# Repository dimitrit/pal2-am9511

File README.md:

AM9511 Module for the PAL-2
===========================

The AMD AM9511 Arithmetic Processing Unit, first produced in the late 
1970s, provides hardware support for high performance fixed and floating 
point arithmetic and a variety of floating point trigonometric and 
mathematical operations, for use with microprocessors of that period.

This repository provides schematics and board design for a module that
can be connected to the PAL-2 Expansion interface.

The design is adapted from the work of Harris[1], who in turn based 
his implementation on designs by Kissel and Currie[2] in which they 
developed an experiment using a MOS 6502 microprocessor to control 
four AM9511A floating-point arithmetic units, and from Hart’s 
MICROCRUNCH[3] which also used the AM9511A (Intel 8231A) interfaced 
with a (Rockwell) 6502.

See [am9511-6502-description.pdf](am9511-6502-description.pdf) for a
full description of the interface circuit design and 
[am9511-6502-schematic.pdf](am9511-6502-schematic.pdf) for the schematic.

The specification here anticipates the use of an AM9511A clocked at
4 MHz. However, the same design will work with earlier versions of the 
AM9511, by setting JP to 2Mhz or by swapping the 4 MHz clock oscillator 
with a unit of an appropriately lower speed.

The `logic` folder contains the programming details for the ATF16V8B
used in the circuit, as produced by [Galette](https://github.com/simon-frankau/galette) 
from the `am9511-logic.pld` source file. The provided JEDEC file
(`am9511-logic.jed`) can be easily programmed into an ATF16V8B using 
[minipro](https://gitlab.com/DavidGriffith/minipro).

Also included in the `docs` folder are source documents cited below, as 
well as datasheets and supplementary documents for the AM9511.

---
1. Harris, CE: "AM9511 Interface Module for the 6502"; July 2025; [GitHub](https://github.com/ceharris/am9511-6502)
2. Kissel, R and Currie, J: "Hardware Math for the 6502 Microprocessor"; 
   July 1985; NASA TM-86517
3. Hart, J: "MICROCRUNCH: An Ultra-Fast Arithmetic Computing System 
   (part 1)"; August 1981; MICRO - the 6502/6809 Journal (No. 39)

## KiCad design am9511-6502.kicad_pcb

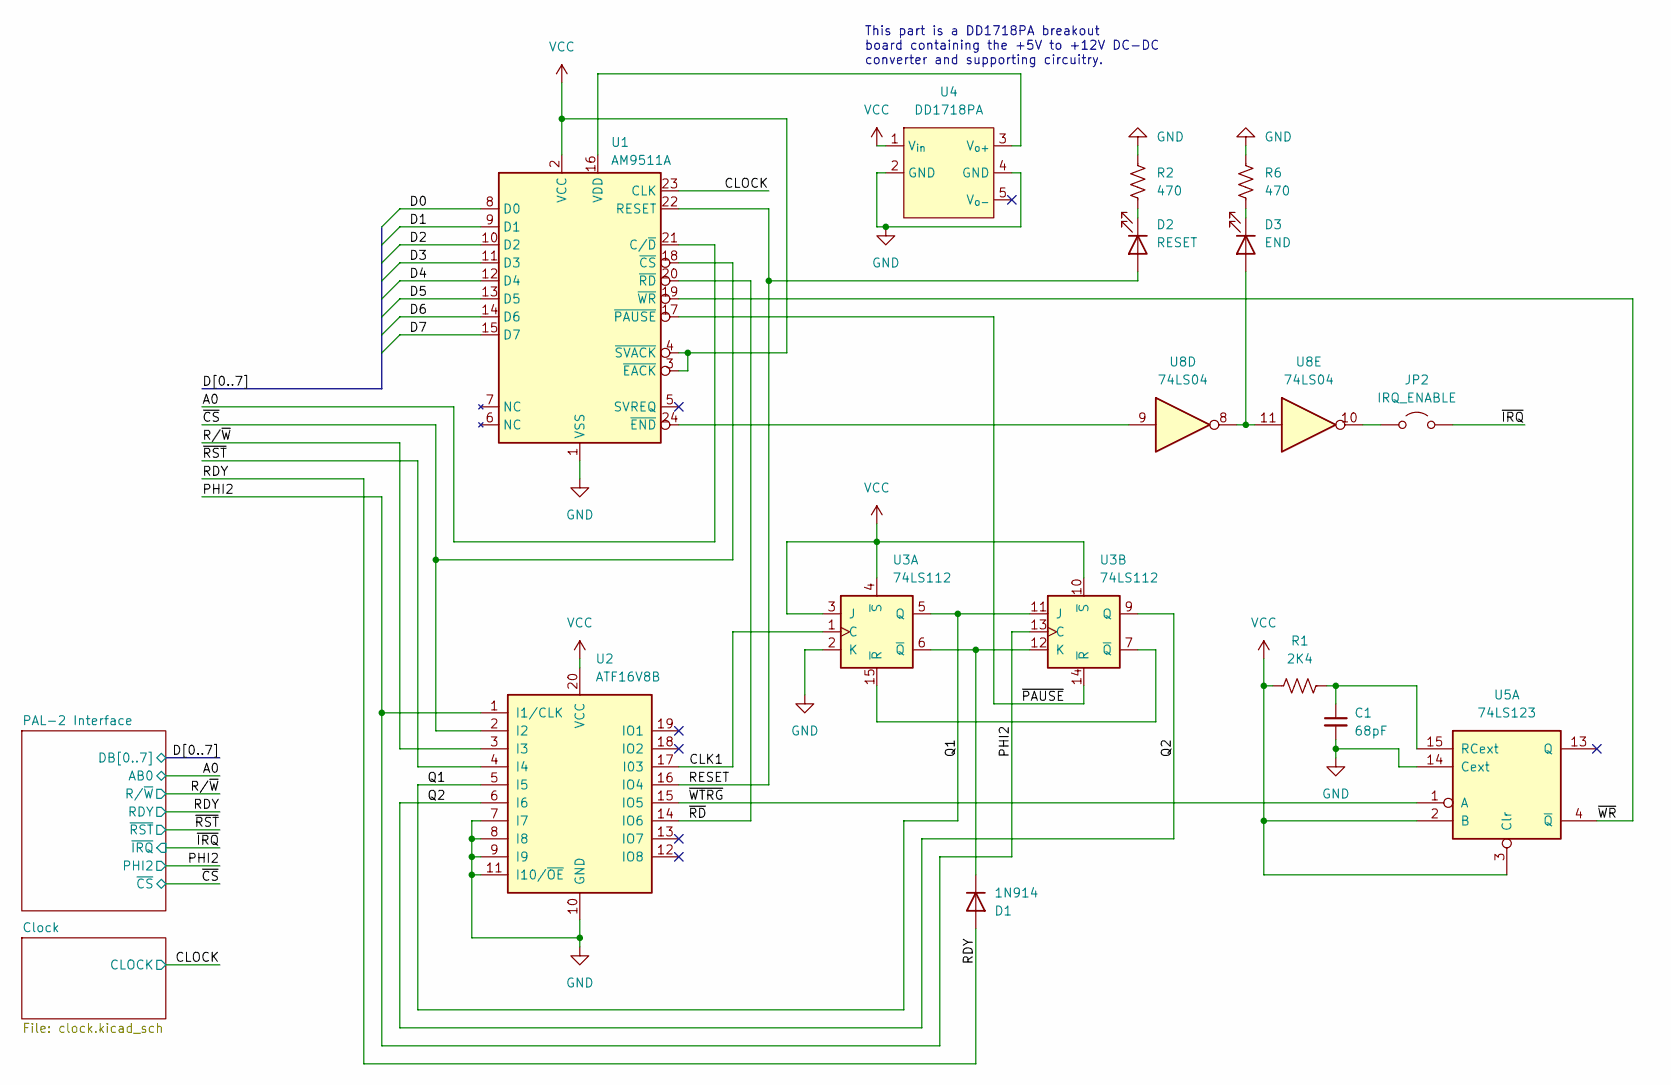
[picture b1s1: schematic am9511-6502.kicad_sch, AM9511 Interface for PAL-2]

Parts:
C1: 68pF; C_Disc_D5.0mm_W2.5mm_P5.00mm
D1: 1N914; D_DO-35_SOD27_P7.62mm_Horizontal
D2: RESET; LED_D3.0mm
D3: END; LED_D3.0mm
JP2: IRQ_ENABLE; PinHeader_1x02_P2.54mm_Vertical
R1: 2K4; R_Axial_DIN0207_L6.3mm_D2.5mm_P7.62mm_Horizontal
R2, R6: 470; R_Axial_DIN0207_L6.3mm_D2.5mm_P7.62mm_Horizontal
U1: AM9511A; DIP-24_W15.24mm_Socket
U2: ATF16V8B; DIP-20_W7.62mm_Socket
U3: 74LS112; DIP-16_W7.62mm_Socket
U4: DD1718PA
U5: 74LS123; DIP-16_W7.62mm_Socket
U8: 74LS04; DIP-14_W7.62mm_Socket

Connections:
/A0: U1.21 (C/~D); also elsewhere on the board
/CLK1: U2.17 (I03), U3.1 (C)
/CLOCK: U1.23 (CLK); also elsewhere on the board
/D0: U1.8 (D0); also elsewhere on the board
/D1: U1.9 (D1); also elsewhere on the board
/D2: U1.10 (D2); also elsewhere on the board
/D3: U1.11 (D3); also elsewhere on the board
/D4: U1.12 (D4); also elsewhere on the board
/D5: U1.13 (D5); also elsewhere on the board
/D6: U1.14 (D6); also elsewhere on the board
/D7: U1.15 (D7); also elsewhere on the board
/PHI2: U2.1 (I1/CLK), U3.13 (C); also elsewhere on the board
/Q1: U2.5 (I5), U3.5 (Q), U3.11 (J)
/Q2: U2.6 (I6), U3.9 (Q)
/RDY: D1.2 (A); also elsewhere on the board
/RESET: D2.2 (A), U1.22 (RESET), U2.16 (IO4)
/R/~W: U2.3 (I3); also elsewhere on the board
/~CS: U1.18 (~CS), U2.2 (I2); also elsewhere on the board
/~IRQ: JP2.1 (A); also elsewhere on the board
/~PAUSE: U1.17 (~PAUSE), U3.14 (~R)
/~RD: U1.20 (~RD), U2.14 (IO6)
/~RST: U2.4 (I4); also elsewhere on the board
/~WR: U1.19 (~WR), U5.4 (~Q)
/~WTRG: U2.15 (IO5), U5.1 (A)
GND: C1.2, R2.1, R6.1, U1.1 (VSS), U2.7 (I7), U2.8 (I8), U2.9 (I9), U2.10 (GND), U2.11 (I10/~OE), U3.2 (K), U4.2 (GND), U4.4 (GND), U5.14 (Cext); also elsewhere on the board
unnamed: D1.1 (K), U3.6 (~Q), U3.12 (K)
unnamed: D2.1 (K), R2.2
unnamed: D3.2 (A), U8.8, U8.11
unnamed: D3.1 (K), R6.2
unnamed: JP2.2 (B), U8.10
unnamed: U1.16 (VDD), U4.3 (V_{o+})
unnamed: U1.24 (~END), U8.9
unnamed: U3.7 (~Q), U3.15 (~R)
unnamed: C1.1, R1.2, U5.15 (RCext)
VCC: R1.1, U1.2 (VCC), U1.3 (~EACK), U1.4 (~SVACK), U2.20 (VCC), U3.3 (J), U3.4 (~S), U3.10 (~S), U4.1 (V_{in}), U5.2 (B), U5.3 (Clr); also elsewhere on the board

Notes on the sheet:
This part is a DD1718PA breakout board containing the +5V to +12V DC-DC converter and supporting circuitry.

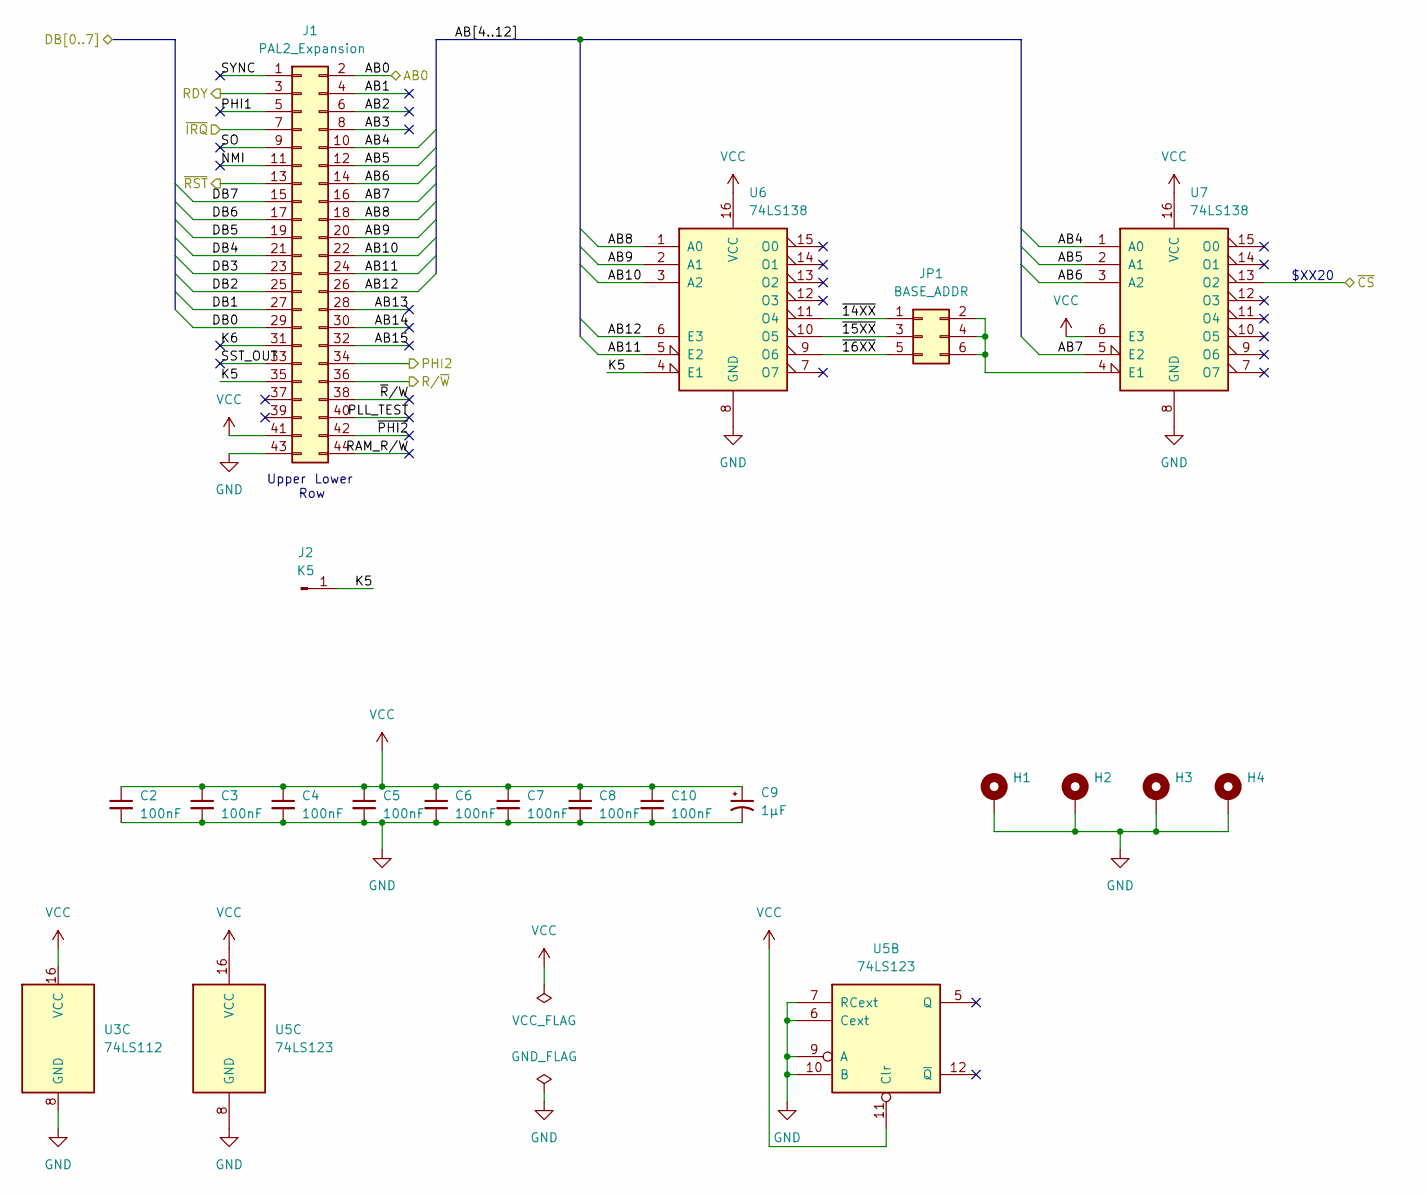
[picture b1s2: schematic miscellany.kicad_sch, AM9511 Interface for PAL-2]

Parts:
C2, C3, C4, C5, C6, C7, C8, C10: 100nF; C_Disc_D5.0mm_W2.5mm_P2.50mm
C9: 1µF; CP_Radial_D5.0mm_P2.50mm
H1, H2, H3, H4: MountingHole_Pad; MountingHole_2.2mm_M2_DIN965_Pad
J1: PAL2_Expansion; PinHeader_2x22_P2.54mm_Horizontal
J2: K5; PinHeader_1x01_P2.54mm_Horizontal
JP1: BASE_ADDR; PinHeader_2x03_P2.54mm_Vertical
U3: 74LS112; DIP-16_W7.62mm_Socket
U5: 74LS123; DIP-16_W7.62mm_Socket
U6, U7: 74LS138; DIP-16_W7.62mm_Socket

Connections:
/A0: J1.2; also elsewhere on the board
/D0: J1.29; also elsewhere on the board
/D1: J1.27; also elsewhere on the board
/D2: J1.25; also elsewhere on the board
/D3: J1.23; also elsewhere on the board
/D4: J1.21; also elsewhere on the board
/D5: J1.19; also elsewhere on the board
/D6: J1.17; also elsewhere on the board
/D7: J1.15; also elsewhere on the board
/PAL-2 Interface/AB1: J1.4
/PAL-2 Interface/AB2: J1.6
/PAL-2 Interface/AB3: J1.8
/PAL-2 Interface/AB4: J1.10, U7.1 (A0)
/PAL-2 Interface/AB5: J1.12, U7.2 (A1)
/PAL-2 Interface/AB6: J1.14, U7.3 (A2)
/PAL-2 Interface/AB7: J1.16, U7.5 (E2)
/PAL-2 Interface/AB8: J1.18, U6.1 (A0)
/PAL-2 Interface/AB9: J1.20, U6.2 (A1)
/PAL-2 Interface/AB10: J1.22, U6.3 (A2)
/PAL-2 Interface/AB11: J1.24, U6.5 (E2)
/PAL-2 Interface/AB12: J1.26, U6.6 (E3)
/PAL-2 Interface/AB13: J1.28
/PAL-2 Interface/AB14: J1.30
/PAL-2 Interface/AB15: J1.32
/PAL-2 Interface/K5: J1.35, J2.1, U6.4 (E1)
/PAL-2 Interface/K6: J1.31
/PAL-2 Interface/NMI: J1.11
/PAL-2 Interface/PHI1: J1.5
/PAL-2 Interface/PLL_TEST: J1.40
/PAL-2 Interface/RAM_R/W: J1.44
/PAL-2 Interface/SO: J1.9
/PAL-2 Interface/SST_OUT: J1.33
/PAL-2 Interface/SYNC: J1.1
/PAL-2 Interface/~14XX: JP1.1, U6.11 (O4)
/PAL-2 Interface/~15XX: JP1.3, U6.10 (O5)
/PAL-2 Interface/~16XX: JP1.5, U6.9 (O6)
/PAL-2 Interface/~PHI2: J1.42
/PAL-2 Interface/~R/W: J1.38
/PHI2: J1.34; also elsewhere on the board
/RDY: J1.3; also elsewhere on the board
/R/~W: J1.36; also elsewhere on the board
/~CS: U7.13 (O2); also elsewhere on the board
/~IRQ: J1.7; also elsewhere on the board
/~RST: J1.13; also elsewhere on the board
GND: C2.2, C3.2, C4.2, C5.2, C6.2, C7.2, C8.2, C9.2, C10.2, H1.1, H2.1, H3.1, H4.1, J1.43, U3.8 (GND), U5.6 (Cext), U5.7 (RCext), U5.8 (GND), U5.9 (A), U5.10 (B), U6.8 (GND), U7.8 (GND); also elsewhere on the board
unnamed: JP1.2, JP1.4, JP1.6, U7.4 (E1)
VCC: C2.1, C3.1, C4.1, C5.1, C6.1, C7.1, C8.1, C9.1, C10.1, J1.41, U3.16 (VCC), U5.11 (Clr), U5.16 (VCC), U6.16 (VCC), U7.6 (E3), U7.16 (VCC); also elsewhere on the board

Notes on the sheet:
Lower
Upper
$XX20
Row

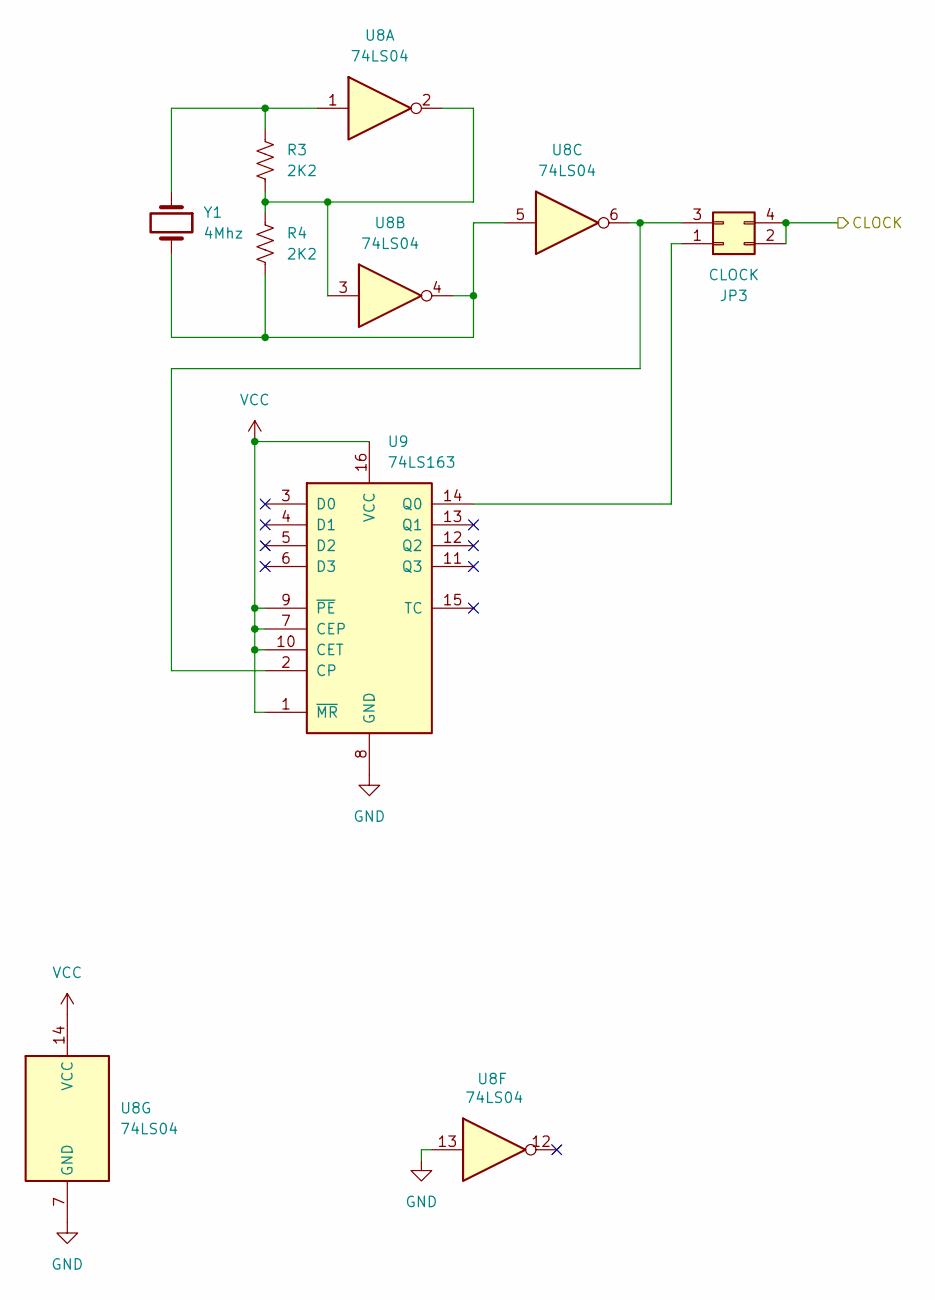
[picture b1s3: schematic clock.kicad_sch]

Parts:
JP3: CLOCK; PinHeader_2x02_P2.54mm_Vertical
R3, R4: 2K2; R_Axial_DIN0207_L6.3mm_D2.5mm_P7.62mm_Horizontal
U8: 74LS04
U9: 74LS163; DIP-16_W7.62mm_Socket
Y1: 4Mhz; Crystal_HC49-4H_Vertical

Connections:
/CLOCK: JP3.2, JP3.4; also elsewhere on the board
GND: U8.7 (GND), U8.13, U9.8 (GND); also elsewhere on the board
unnamed: JP3.1, U9.14 (Q0)
unnamed: JP3.3, U8.6, U9.2 (CP)
unnamed: R3.1, R4.2, U8.2, U8.3
unnamed: R3.2, U8.1, Y1.1
unnamed: R4.1, U8.4, U8.5, Y1.2
VCC: U8.14 (VCC), U9.1 (~MR), U9.7 (CEP), U9.9 (~PE), U9.10 (CET), U9.16 (VCC); also elsewhere on the board

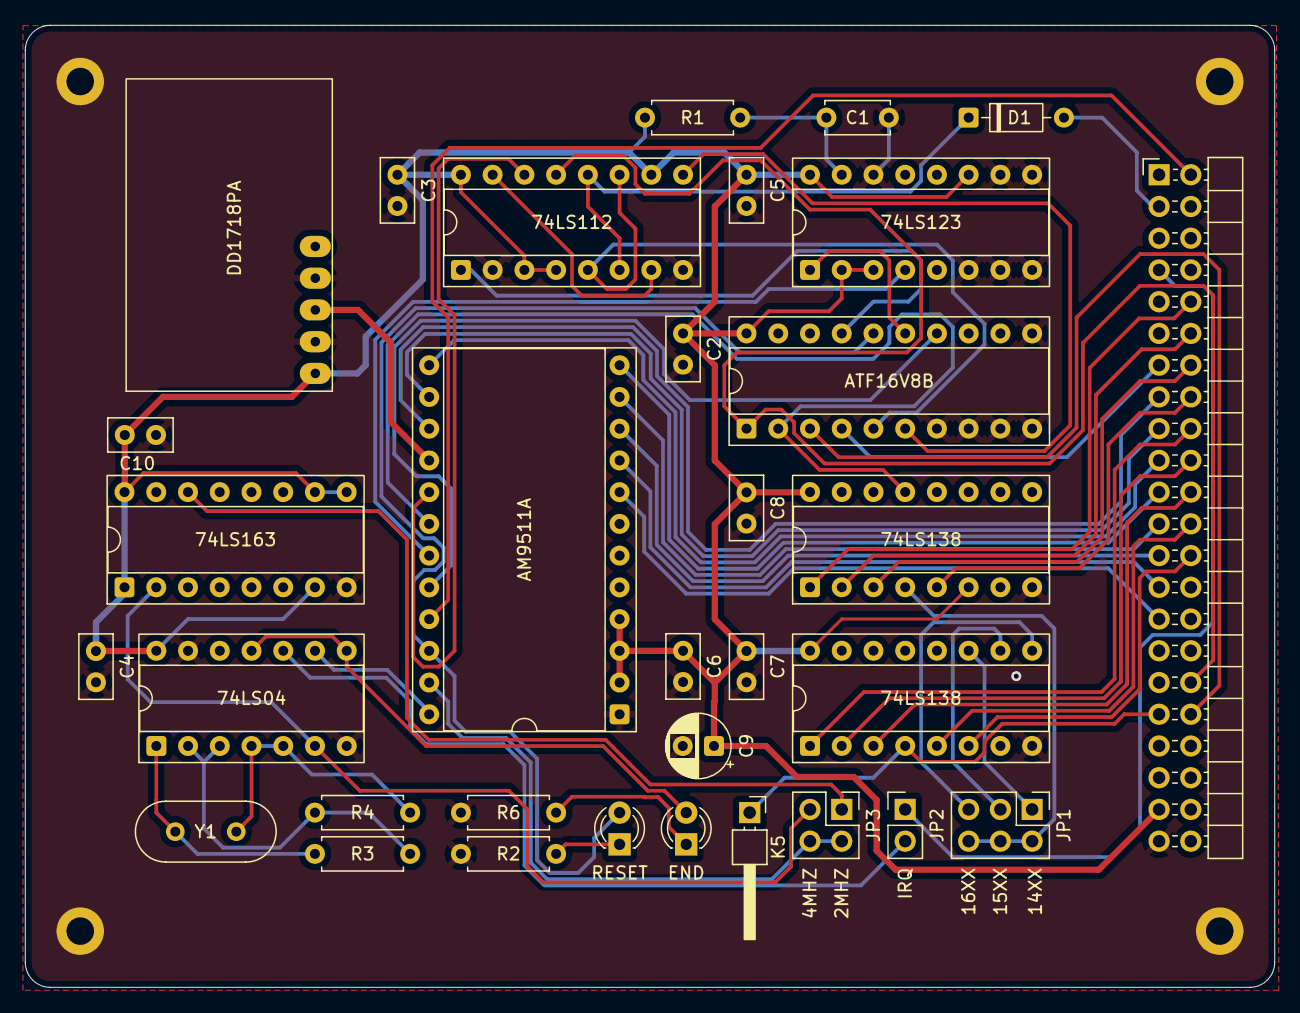
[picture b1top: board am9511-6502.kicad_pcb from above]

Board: 2 copper layers, 100.0 x 77.0 mm, 37 parts (0 on the bottom side), 54 nets.

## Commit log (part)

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2025-07-10 additional PCB cleanup
2025-07-10 convert full description from orig google doc to latex
2025-07-10 additional description text revisions
2025-07-10 include gerbers in the repo
2025-07-10 minor revisions to description document
2025-07-11 reset schematic annotations
2025-07-11 create instructions.md to help avoid release mistakes
2025-07-11 revise PLD source to be consistent with documentation
2025-07-24 add photo of board
2025-07-26 minor revisions to circuit description
2025-07-26 add PCBway review
2025-07-26 fix review link
2025-07-26 add final remark to README
2025-07-26 add PCBWay links on main page
2025-07-26 minor README improvements

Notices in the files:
am9511-6502.kicad_sch:
CC BY 4.0
